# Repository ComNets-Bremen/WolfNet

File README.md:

WolfNet - A simple LoRa based network for deterrents
====================================================

The [mAInZaun-Project](https://intelligenter-herdenschutz.de/) is aiming on
extending existing fence by using adaptive deterrents to scare away predators.

This part implements a simple protocol for the sensors and actuators: How can
the deterrents be activated wirelessly if a predator is detected?

For that, we created our own, hand-crafted protocol using LoRa. The main packet formats are described in the file [packets.md](packets.md) in this directory.

The complete stack is written in [Micropython](https://micropython.org) and using [Heltec WiFi LoRa 32 v2](https://heltec.org/project/wifi-lora-32/) nodes. A migration to [Heltec WiFi LoRa 32 v3](https://heltec.org/project/wifi-lora-32-v3/) is planned in [this issue](../../issues/1).

Programming is done in [Visual Studio Code](https://code.visualstudio.com/) using the [pymakr-plugin](https://github.com/pycom/pymakr-vsc). If you are getting an error while running the pymakr-plugin: Make sure you have installed NodeJS!

What is in the subdirectories?
==============================

controlbox
----------

The idea is to have a box for the management of the complete (LoRa) system. It
should have a touchscreen and basic interface for changing parameters like
beaconing intervals or reading out the battery state.

Datasheets
----------

Collection of all relevant datasheets

Schematic
---------

Contains the schematics as KICad files -- currently mainly the ones for the
actuator boxes.

tools
-----

General tools which might be handy for debugging

wolfnet
-------

The firmware itself which makes the sensors and the actuators communicate. It
is a Visual Studio Code project and using the Pymakr-plugin.

Issues
======

The known issues can be found in the [github issue tracker](../../issues)

License
=======

WolfNet
-------

The license of the code can be found in the [LICENSE](LICENSE) file.

3rd Party
---------

- The used AES library is licensed using the MIT license and available here: https://github.com/iyassou/mpyaes
- The driver sx127x.py for the sx127x LoRa transceiver is licensed under the Apache 2.0 license and available here: https://github.com/lemariva/uPyLoRaWAN

Authors
=======

- Jens Dede, ComNets University of Bremen, jd@comnets.uni-bremen.de
- Lars Gerken, University of Bremen, lagerken@uni-bremen.de

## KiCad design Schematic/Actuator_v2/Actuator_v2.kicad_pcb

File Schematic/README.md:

Source model: https://github.com/Heltec-Aaron-Lee/WiFi_Kit_series/tree/master/Kicad5_lib_footprint/Heltec_wifi_LoRa_V1

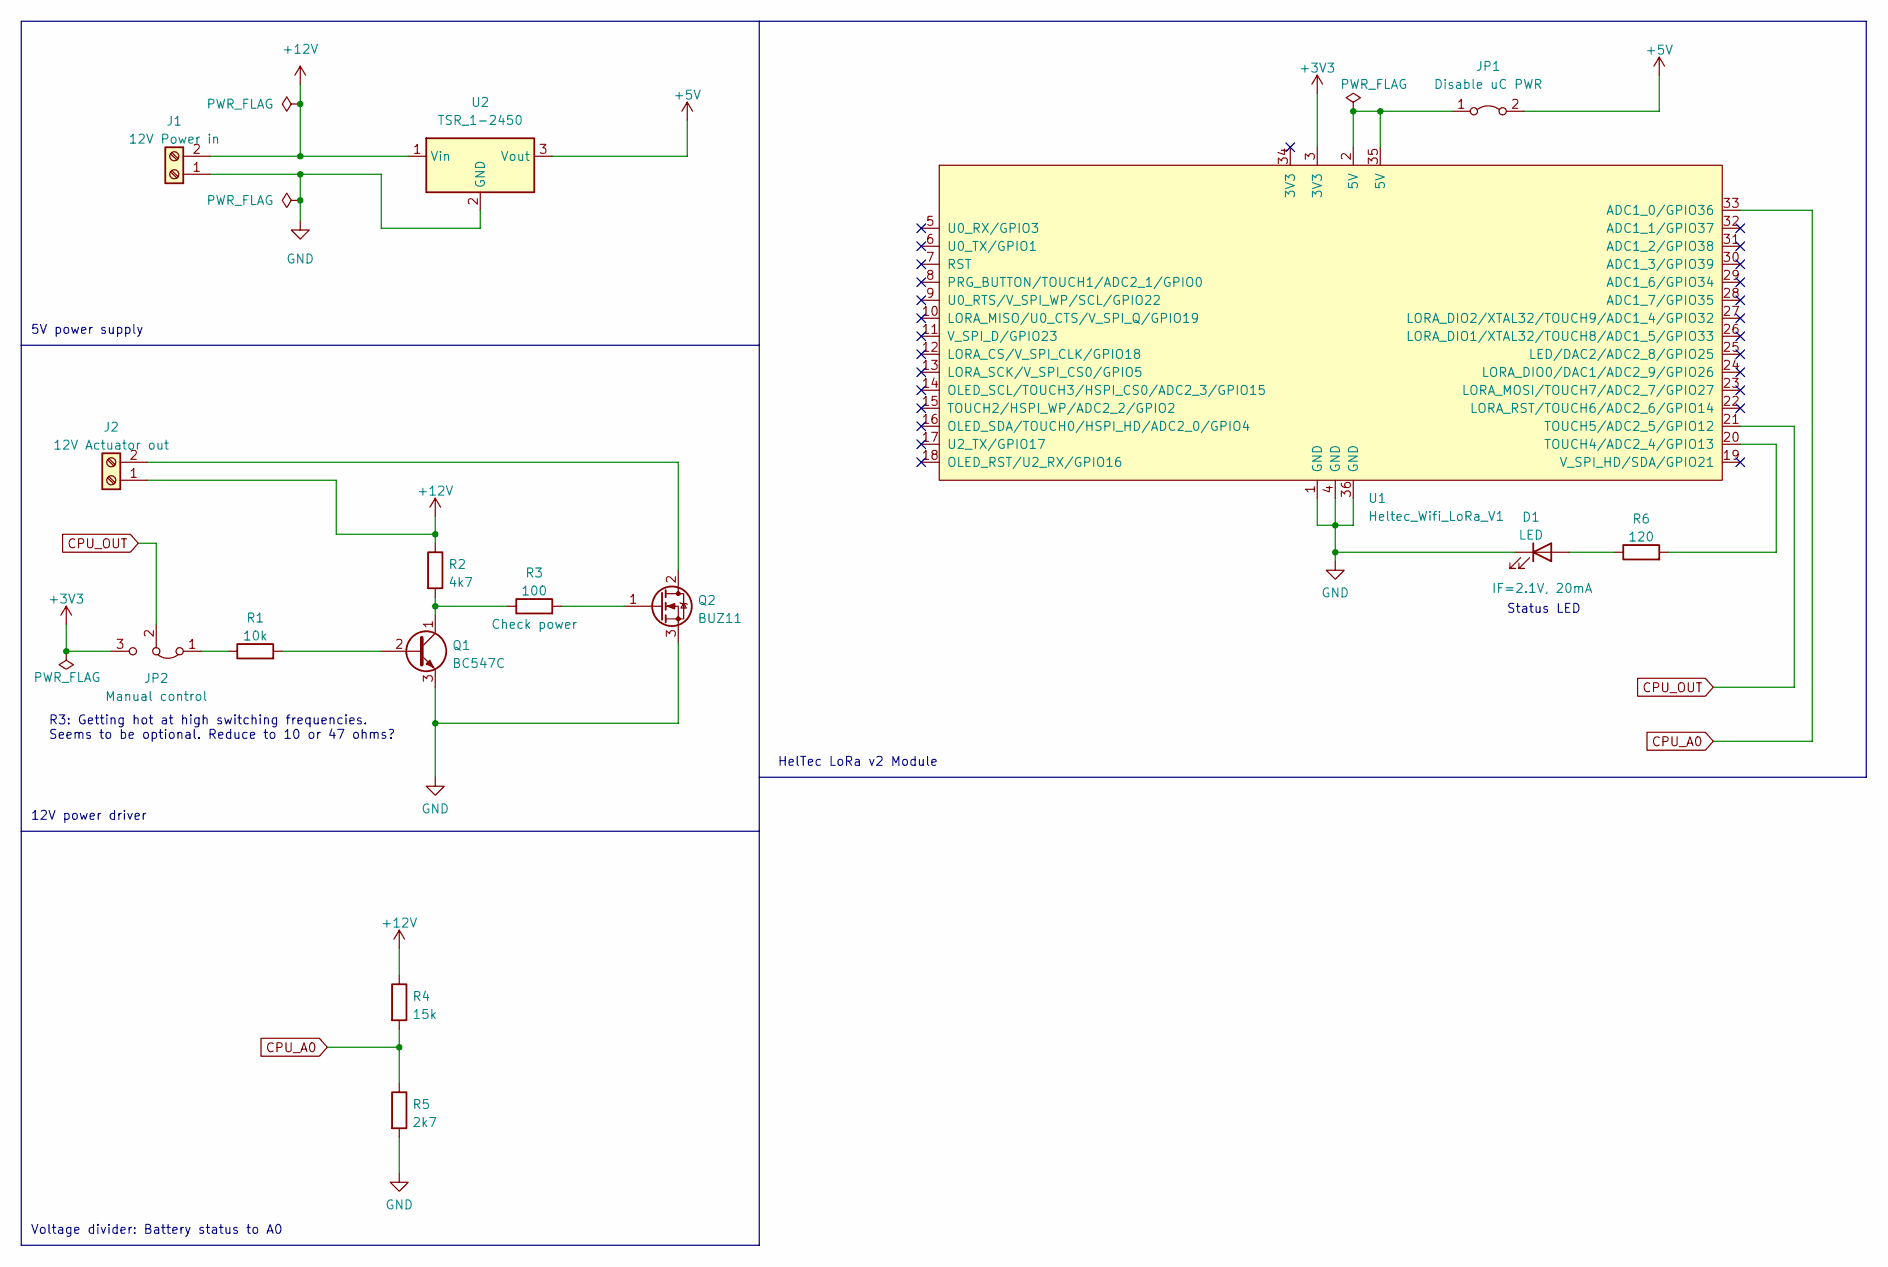
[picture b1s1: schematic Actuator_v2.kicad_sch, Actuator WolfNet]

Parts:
D1: LED; LED_D5.0mm_IRGrey
J1: 12V Power in; TerminalBlock_RND_205-00001_1x02_P5.00mm_Horizontal
J2: 12V Actuator out; TerminalBlock_RND_205-00001_1x02_P5.00mm_Horizontal
JP1: Disable uC PWR; PinHeader_1x02_P2.54mm_Vertical
JP2: Manual control; PinHeader_1x03_P2.54mm_Vertical
Q1: BC547C; TO-92_Inline
Q2: BUZ11; TO-220-3_Vertical
R1: 10k; R_Axial_DIN0411_L9.9mm_D3.6mm_P12.70mm_Horizontal
R2: 4k7; R_Axial_DIN0411_L9.9mm_D3.6mm_P12.70mm_Horizontal
R3: 100; R_Axial_DIN0411_L9.9mm_D3.6mm_P12.70mm_Horizontal
R4: 15k; R_Axial_DIN0411_L9.9mm_D3.6mm_P12.70mm_Horizontal
R5: 2k7; R_Axial_DIN0411_L9.9mm_D3.6mm_P12.70mm_Horizontal
R6: 120; R_Axial_DIN0411_L9.9mm_D3.6mm_P12.70mm_Horizontal
U1: Heltec_Wifi_LoRa_V1; Heltec_WiFi_LoRa_V1
U2: TSR_1-2450; Converter_DCDC_TRACO_TSR-1_THT

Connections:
+3V3: JP2.3 (B), U1.3 (3V3)
+5V: JP1.2 (B), U2.3 (Vout)
+12V: J1.2, J2.1, R2.1, R4.1, U2.1 (Vin)
CPU_A0: R4.2, R5.1, U1.33 (ADC1_0/GPIO36)
CPU_OUT: JP2.2 (C), U1.21 (TOUCH5/ADC2_5/GPIO12)
GND: D1.1 (K), J1.1, Q1.3 (E), Q2.3 (S), R5.2, U1.1 (GND), U1.4 (GND), U1.36 (GND), U2.2 (GND)
unnamed: D1.2 (A), R6.1
unnamed: J2.2, Q2.2 (D)
unnamed: JP1.1 (A), U1.2 (5V), U1.35 (5V)
unnamed: JP2.1 (A), R1.1
unnamed: Q1.1 (C), R2.2, R3.1
unnamed: Q1.2 (B), R1.2
unnamed: Q2.1 (G), R3.2
unnamed: R6.2, U1.20 (TOUCH4/ADC2_4/GPIO13)

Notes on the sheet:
12V power driver
HelTec LoRa v2 Module
R3: Getting hot at high switching frequencies. Seems to be optional. Reduce to 10 or 47 ohms?
Voltage divider: Battery status to A0
Status LED
5V power supply

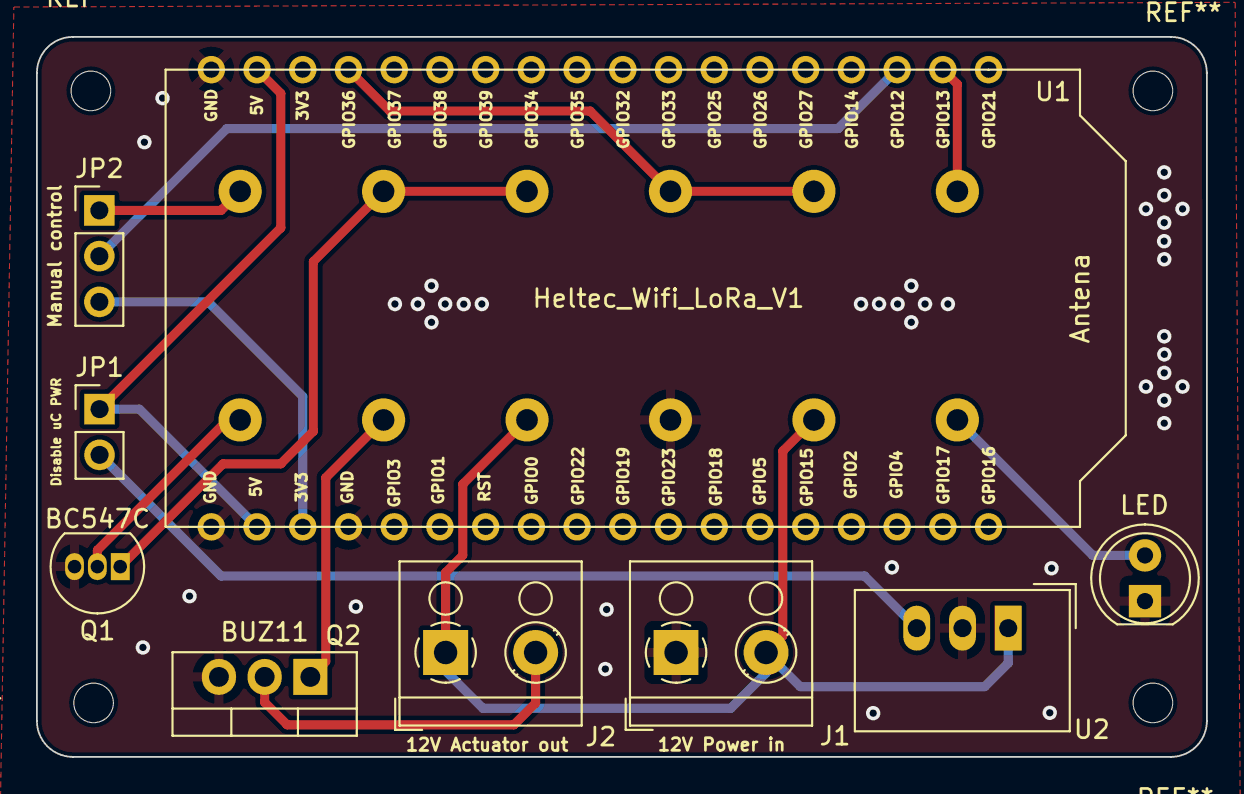
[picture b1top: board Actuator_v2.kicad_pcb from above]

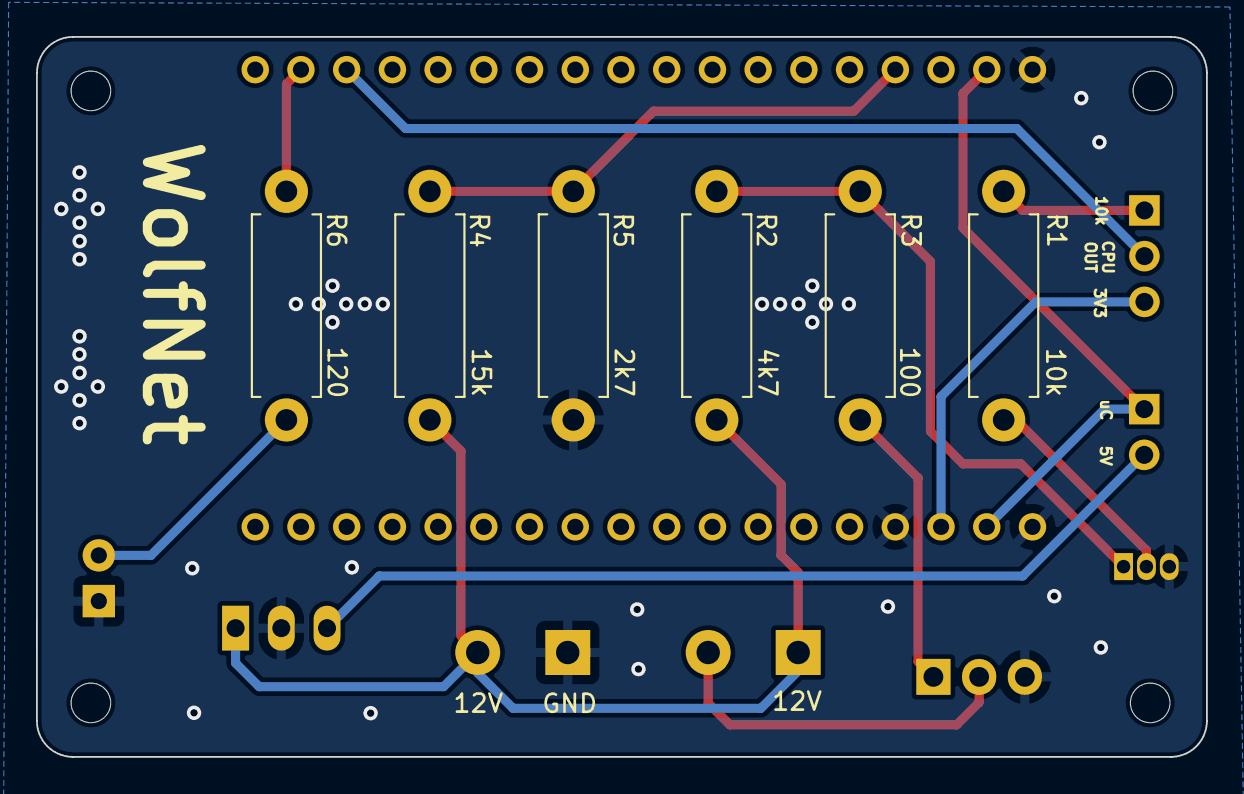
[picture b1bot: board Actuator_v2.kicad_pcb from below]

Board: 2 copper layers, 65.0 x 40.0 mm, 15 parts (6 on the bottom side), 14 nets.

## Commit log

2022-01-10 The actuator firmware for testing and the first fieldtests
2022-01-20 Introduce sniffer mode, allow adding device status to beacons
2022-01-20 Allow battery access using MAX17043 or analog in
2022-01-20 Use the battery handler, use the sniffer node
2022-01-31 Tested analog battery monitor and config for new node
2022-03-02 Reboot if LoRa is not initiated correctly
2022-03-02 Print the version number in case of the error message
2022-03-02 Add more nodes and configs
2022-03-08 New message types, generic actor type
2022-03-08 New blink functions
2022-03-08 Schedule actions using timers, new (more generic) config
2022-03-08 nits
2022-08-17 Bug: Show correct battery status
2022-08-17 Add new node, add new status LED and IRQ config
2022-08-17 Use status LED. Use IRQ only on some nodes (which are having a button)
2023-02-02 Update to most recent version
2023-02-02 Add wolfnet informations, updated structure
2023-03-24 New layout by Eenesh
2023-04-16 Add new boxes, fix status LED
2023-06-06 Formatting fix
2023-06-06 Another minor formatting issue fixed
2023-07-13 Impemented ACK, Block time at receiver side, allow multiple sender to one actor etc. Do not use per-actor-message, stripped down config...
2023-07-17 Just minor comments
2023-07-19 New Schematics
2023-07-19 Add more datasheets
2023-07-19 Add license and ignore file
2023-07-19 Extend readme
2023-07-19 Remove testing firmware: Not being used anymore
2023-07-19 Add some comments to the sniffer script
2023-07-19 Tidy up the datasheet dir a little bit...
2023-07-20 Create packets.md
    Some basic packet definitions for reference
2023-07-20 Ref to packets.md inside the readme.md
2023-07-20 Del Readme in wolfnet-subdirectory
    Information moved to main readme and tickets
2023-07-20 Update README.md
    - Link to issues
    - Added 3rd party licenses
2023-07-20 Update README.md
    Add more project information
2023-07-20 Update README.md
    Relative links to issues on GH
2023-07-20 Update README.md
    We removed the testing firmware
2023-07-20 Use app config, reduce timeout, more debug output regarding RTT and RSSI
2023-07-25 Optimization regarding the next trigger
2023-07-25 New nodes, code formatted
2023-08-01 Do not upload the workspace config
2023-08-01 Bugfix: Do not use an arbitrary device as fuel gauge. Check for the correct address.
2023-08-01 Handle non-existing fuel gauge
2023-08-01 - Show reset reasons - Restart if radio module did not boot correctly - Gracefully stop if node config does not exist - Handle non-existing fuel gauge
2023-08-01 Add a playground node to the config
2023-08-01 Bugfix: Invalid json
2023-08-01 Use None instead of 0 for the battery status: Not transmitted
2023-08-08 Tidy up config: Remove unneeded parts
2023-08-08 Make sure WiFi is really off (does not make a difference in the measured power consumption, just to be at the safe side...)
2023-08-09 added files
2023-08-09 Update README.md
    add lars
2023-09-14 Replaced one node -> new ids
2023-09-18 Connection of RapsberryPi and Dragino
2023-09-18 Update README.md
    Added picture and more details
2023-09-26 Update README.md: Use relative link
